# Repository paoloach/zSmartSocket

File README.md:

# zSmartSocket
zigbee smart socket based on cc2530

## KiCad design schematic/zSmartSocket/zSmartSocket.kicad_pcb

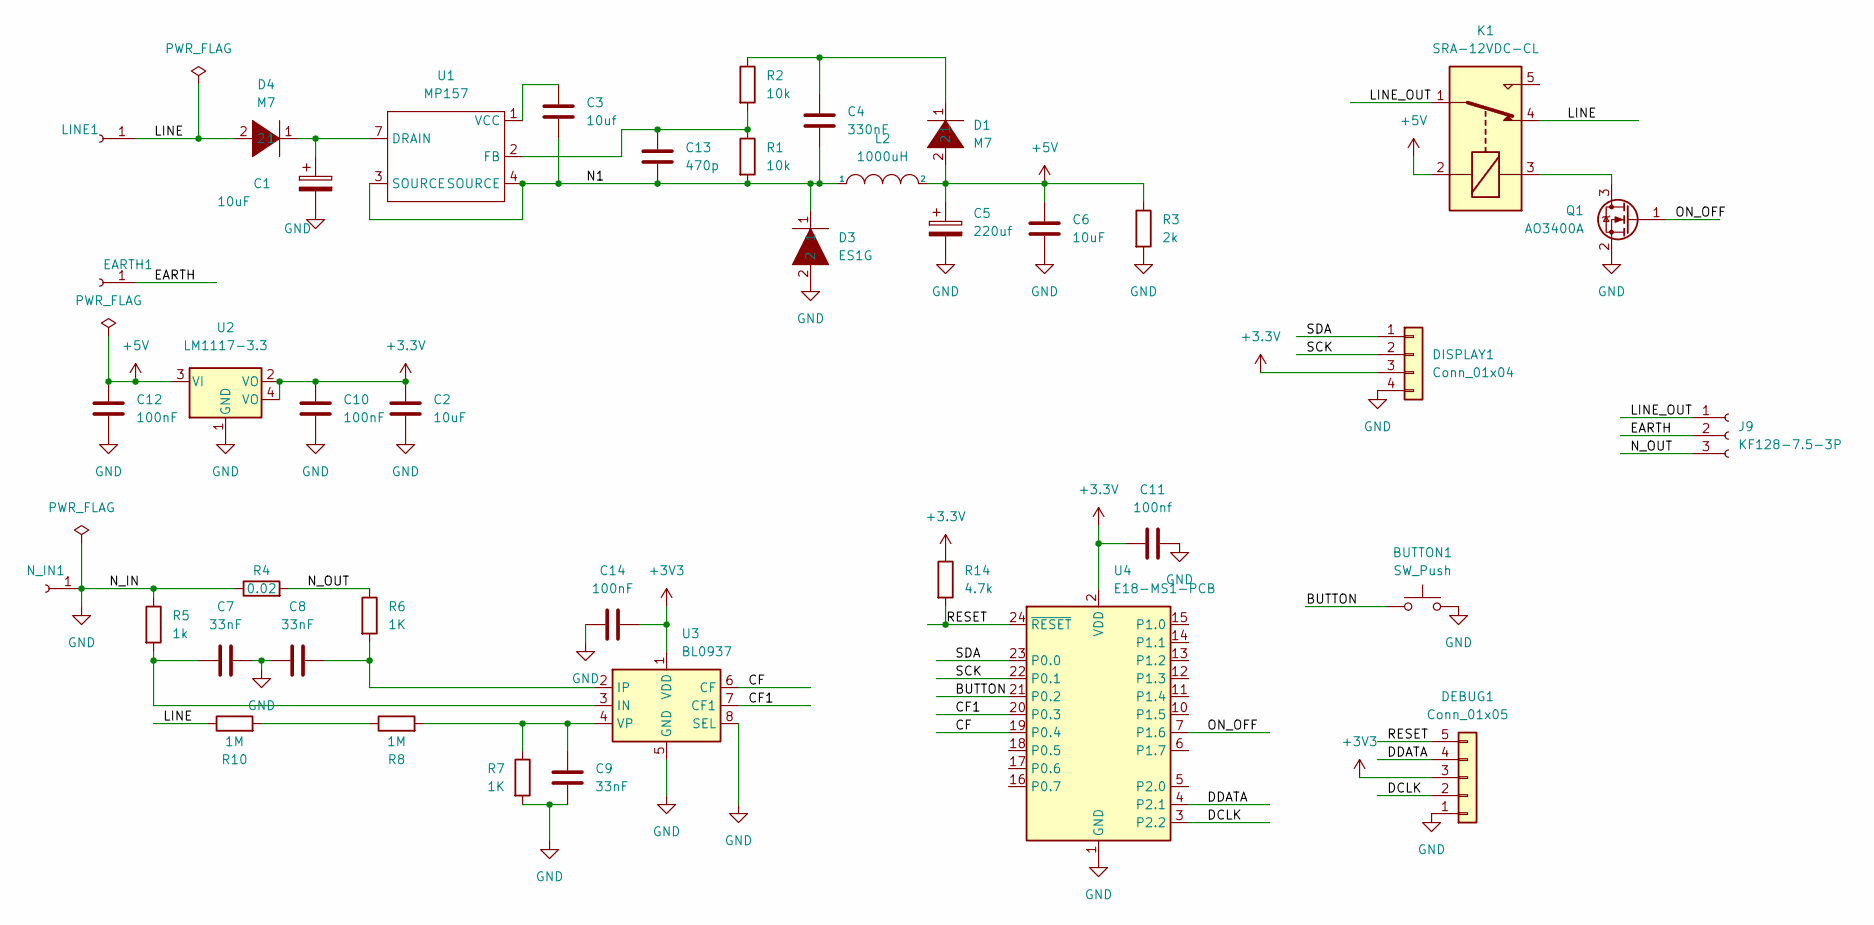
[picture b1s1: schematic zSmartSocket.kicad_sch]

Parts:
BUTTON1: SW_Push; PinHeader_1x02_P2.54mm_Vertical
C1: 10uF; CP_Radial_D10.0mm_P5.00mm
C2, C6: 10uF; C_0603_1608Metric
C3: 10uf; C_0603_1608Metric
C4: 330nF; C_0603_1608Metric
C5: 220uf; CP_Elec_8x10.5
C7, C8, C9: 33nF; C_0603_1608Metric
C10, C12, C14: 100nF; C_0603_1608Metric
C11: 100nf; C_0603_1608Metric
C13: 470p; C_0603_1608Metric
D1, D4: M7; D_SMA
D3: ES1G; D_SMA
DEBUG1: Conn_01x05; PinSocket_1x05_P2.54mm_Vertical
DISPLAY1: Conn_01x04; PinHeader_1x04_P2.54mm_Vertical
EARTH1: Conn_01x01_Female; Pin_D1.4mm_L8.5mm_W2.8mm_FlatFork
J9: KF128-7.5-3P; KF128-7.5_3P
K1: SRA-12VDC-CL; Relay_SPDT_SONGLE_SRA
L2: 1000uH; sumida_CD54
LINE1: Conn_01x01_Female; Pin_D1.4mm_L8.5mm_W2.8mm_FlatFork
N_IN1: Conn_01x01_Female; Pin_D1.4mm_L8.5mm_W2.8mm_FlatFork
Q1: AO3400A; SOT-23
R1, R2: 10k; R_0603_1608Metric
R3: 2k; R_0603_1608Metric
R4: 0.02; ManganeseCooperResistor
R5: 1k; R_0603_1608Metric
R6, R7: 1K; R_0603_1608Metric
R8, R10: 1M; R_0805_2012Metric
R14: 4.7k; R_0603_1608Metric
U1: MP157; SOIC-8_3.9x4.9mm_P1.27mm
U2: LM1117-3.3; SOT-223
U3: BL0937; SOP-8_3.9x4.9mm_P1.27mm
U4: E18-MS1-PCB

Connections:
+5V: C5.1, C6.1, C12.1, D1.2, K1.2, L2.2, R3.1, U2.3 (VI)
/BUTTON: BUTTON1.1, U4.21 (P0.2)
/CF: U3.6 (CF), U4.19 (P0.4)
/CF1: U3.7 (CF1), U4.20 (P0.3)
/DCLK: DEBUG1.2, U4.3 (P2.2)
/DDATA: DEBUG1.4, U4.4 (P2.1)
/EARTH: EARTH1.1, J9.2
/LINE: D4.2, K1.4, LINE1.1, R10.1
/LINE_OUT: J9.1, K1.1
/N1: C3.2, C4.2, C13.2, D3.1, L2.1, R1.2, U1.3 (SOURCE), U1.4 (SOURCE)
/N_OUT: J9.3, R4.2, R6.1
/ON_OFF: Q1.1 (G), U4.7 (P1.6)
/RESET: DEBUG1.5, R14.2, U4.24 (~RESET)
/SCK: DISPLAY1.2, U4.22 (P0.1)
/SDA: DISPLAY1.1, U4.23 (P0.0)
GND: BUTTON1.2, C1.2, C2.2, C5.2, C6.2, C7.2, C8.1, C9.2, C10.2, C11.2, C12.2, C14.1, D3.2, DEBUG1.1, DISPLAY1.4, N_IN1.1, Q1.2 (S), R3.2, R4.1, R5.1, R7.2, U2.1 (GND), U3.5 (GND), U3.8 (SEL), U4.1 (GND)
unnamed: C1.1, D4.1, U1.7 (DRAIN)
unnamed: C3.1, U1.1 (VCC)
unnamed: C4.1, D1.1, R2.1
unnamed: C7.1, R5.2, U3.3 (IN)
unnamed: C8.2, R6.2, U3.2 (IP)
unnamed: C9.1, R7.1, R8.2, U3.4 (VP)
unnamed: C13.1, R1.1, R2.2, U1.2 (FB)
unnamed: K1.3, Q1.3 (D)
unnamed: R8.1, R10.2

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
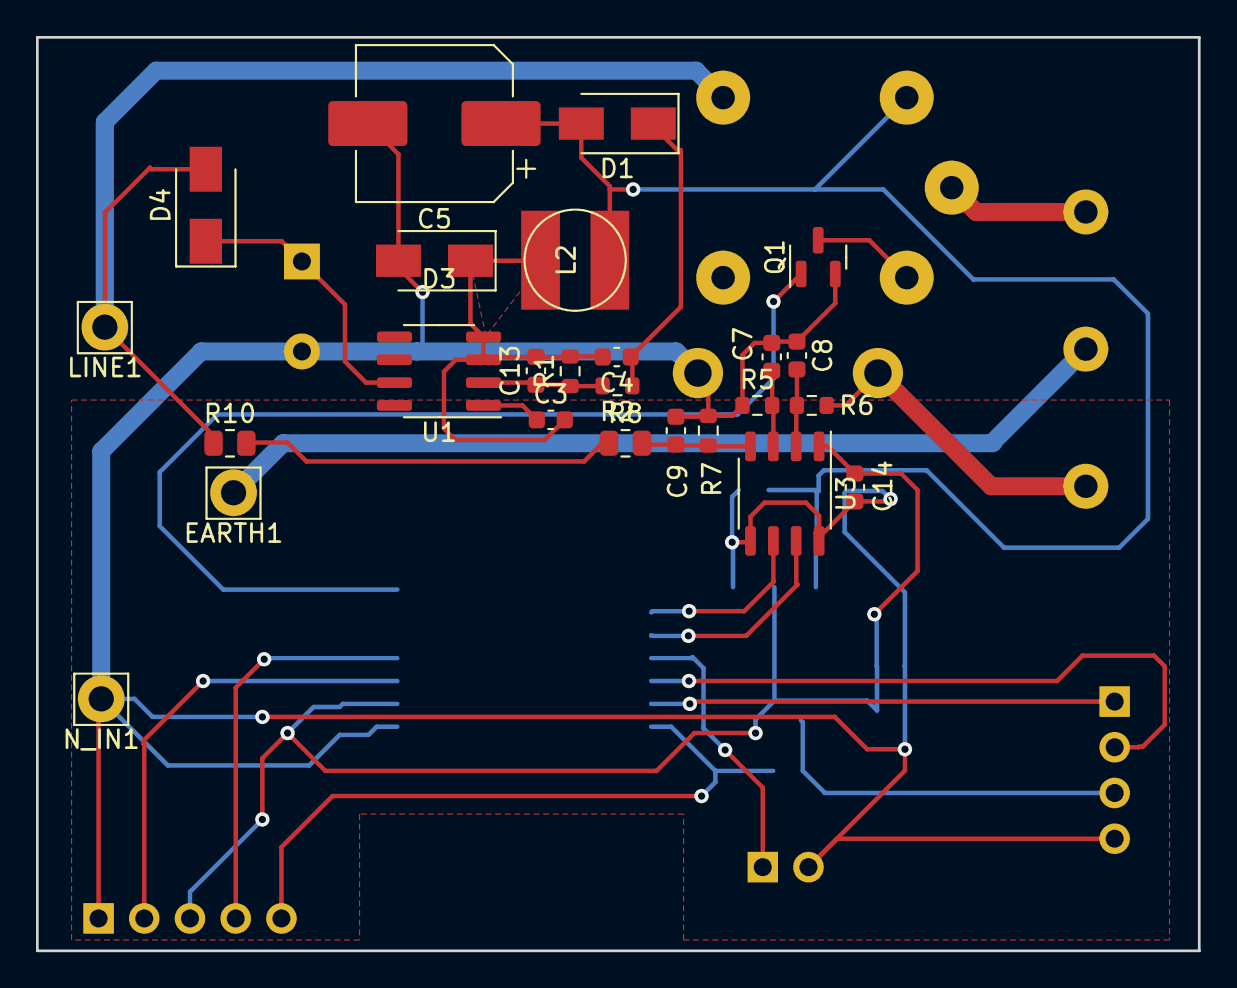
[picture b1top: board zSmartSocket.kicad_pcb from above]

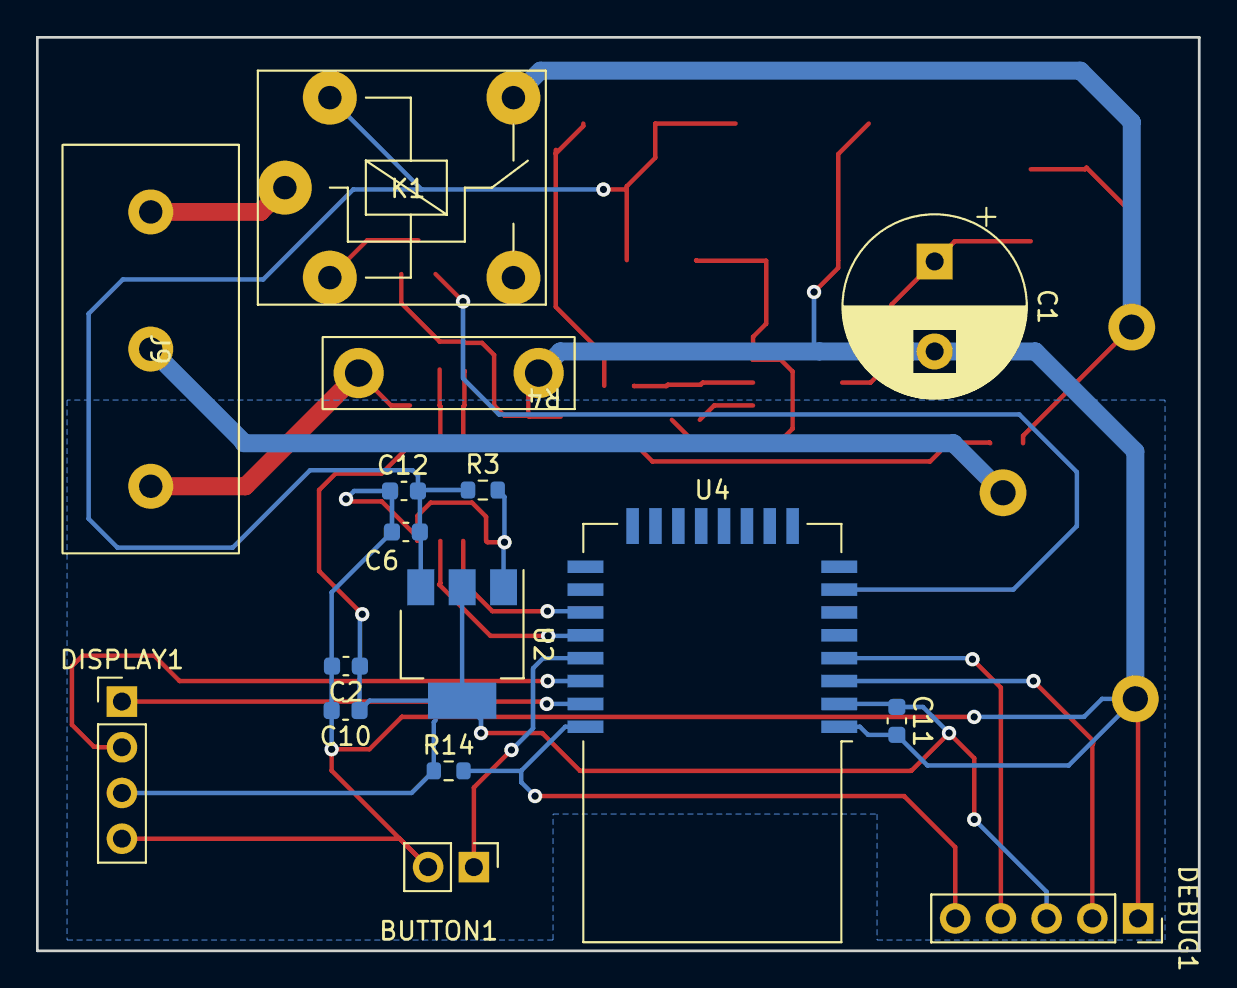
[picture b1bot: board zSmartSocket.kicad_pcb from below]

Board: 2 copper layers, 64.6 x 50.7 mm, 41 parts (16 on the bottom side), 26 nets.

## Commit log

2022-01-25 schematic
